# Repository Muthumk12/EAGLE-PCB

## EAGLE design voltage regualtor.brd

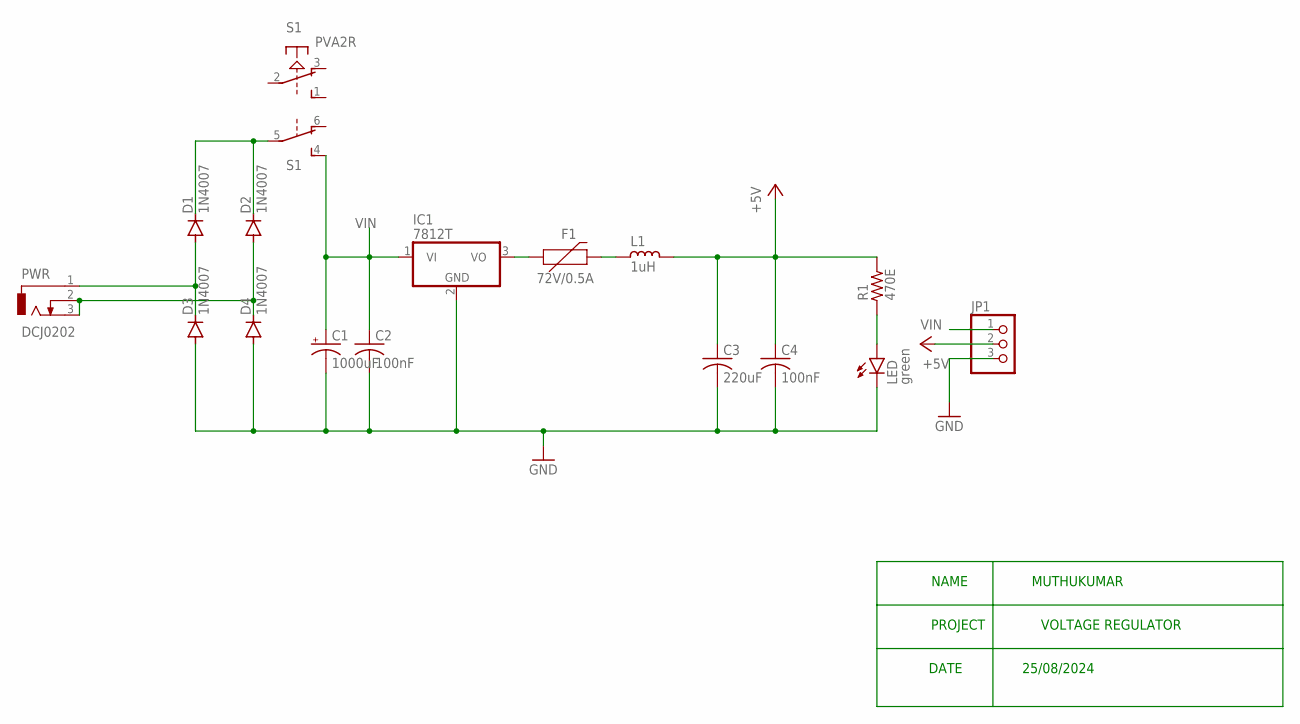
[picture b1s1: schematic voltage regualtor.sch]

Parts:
C1: 1000uF; E5-13
C2, C4: 100nF; C0805
C3: 220uF; C0805
D1, D2, D3, D4: 1N4007; DO41-10
F1: 72V/0.5A; PTH
IC1: 7812T; TO220H
JP1: PINHD-1X3; 1X03
L1: 1uH; L0805
LED: green; CHIPLED_0805
PWR: DCJ0202
R1: 470E; R0805
S1: PVA2R

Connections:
+5V: C3.1, C4.1, JP1.2, L1.1, R1.2
GND: C1.-, C2.2, C3.2, C4.2, D3.A, D4.A, IC1.2 (GND), JP1.3, LED.C
unnamed: D1.C, D2.C, S1.5
unnamed: D1.A, D3.C, PWR.1
unnamed: D2.A, D4.C, PWR.2, PWR.3
unnamed: F1.P$1 (1), IC1.3 (VO)
unnamed: F1.P$2 (2), L1.2
unnamed: LED.A, R1.1
VIN: C1.+, C2.1, IC1.1 (VI), JP1.1, S1.4 (S)

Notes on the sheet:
NAME MUTHUKUMAR
PROJECT VOLTAGE REGULATOR
DATE 25/08/2024

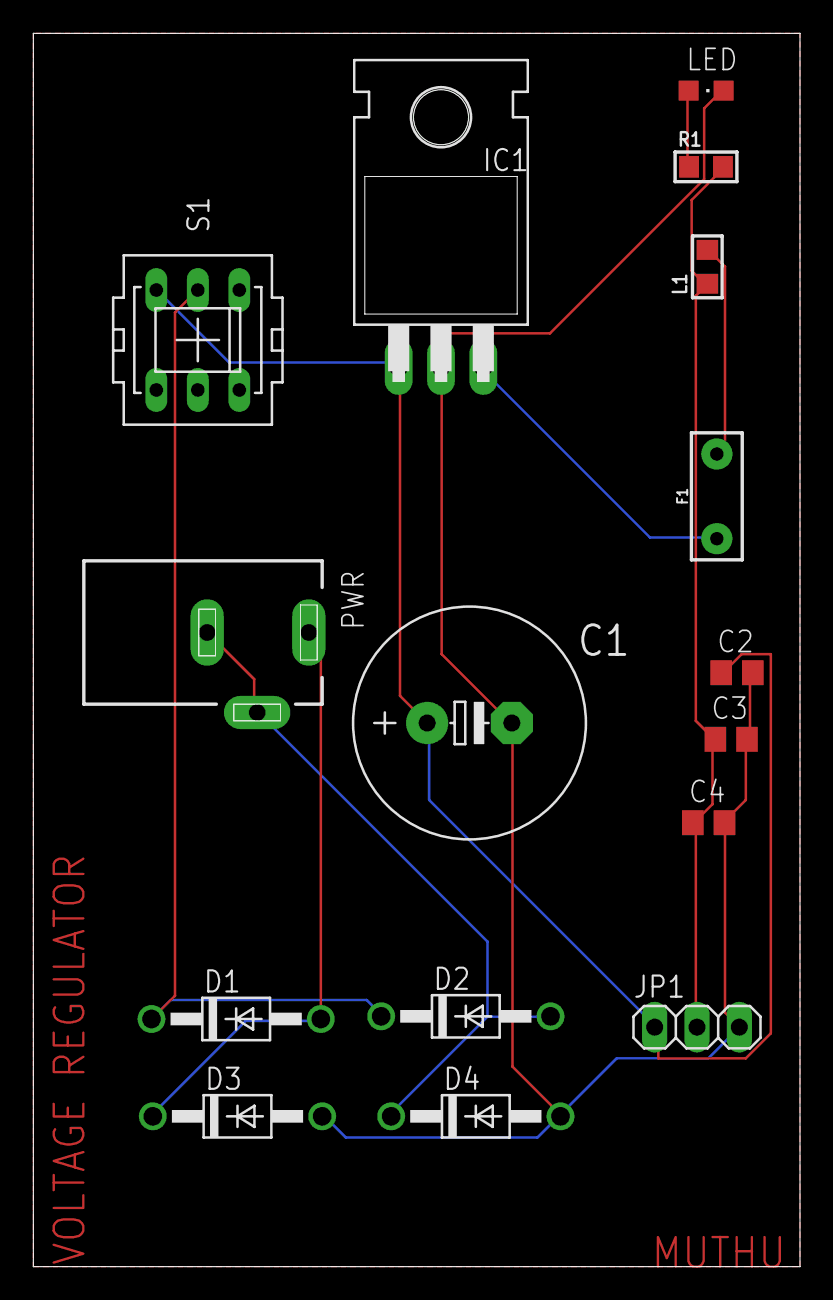
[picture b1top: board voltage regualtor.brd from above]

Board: 2 copper layers, 46.0 x 74.0 mm, 16 parts (0 on the bottom side), 9 nets.

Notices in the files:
parts and their libraries:
SparkFun-Fuses: Licensing: Creative Commons ShareAlike 4.0 International - https://creativecommons.org/licenses/by-sa/4.0
rc-master-smd: Copyright (C) 2007, Bob Starr
